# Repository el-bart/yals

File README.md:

# YALS: Yet Another Linear Servo

project to build a linear servo for RC models.

## key project assumptions

* long move range
* digital position control
* digital feedback on current servo position
* 12V power supply (directly from battery)
* does not consume power when not moving, while still keeping position
* possible magnetic coupling with element moved
* programmable and persistent:
  * min / max positions
  * LED brightness

## building

TL;DR just run `make` from project's root directory.

toolchain has been dockerized.
to make usage more convenient, there's a top-level `Makefile` to run all the elements.
it automatically keeps dependsncies in place.

generated stuff:
* 3D models for printing:
  * all in: `body/build/voron_24_revo/petg/strength/*.gcode`
  * note that there can be >1 carriage to choose from
* electronics (HW):
  * gerber files for PCB: `board/hw/build/gerber.zip`
  * PCB assembly: `board/hw/build/graphics/`
  * BOM: `board/hw/build/bom.csv`
* software (SW):
  * to flash use `./rp2020_sdk rp2040_flash <name_of_binary.elf>` from `board/sw` directory
  * binaries:
    * controller to flash (production): `board/sw/build/rp2040/servo_ctrl.elf`
    * manual tests (for validation of HW assembly):
      * `board/sw/build/rp2040/Hal/rp2040/Hal_*.mtest.elf`
      * `board/sw/build/rp2040/Utils/*.mtest.elf`

## assembly

### BOM
* 1x PCB assembly (see `baord/hw` - build it to get `board/hw/build/bom.csv`)
* 1x MT44 DC motor
* 2x 3x7x3mm ball bearing
* 1x 3mm-3mm universal joing (aka: Cardan joint)
* 1x 3mm threaded rod (~12cm)
* 3x 3mm threaded inset (1x for carriage and 2x for engine)
* 2x M3x14 screws (engine mount)
* 2x M3x10 screws (potentiometer mount)

### tools
* soldering iron
* 3D printer for YALS' body
* hex-key set
* pico-probe or raspberry pi SBC to flash `rp2040` µC

## FAQ

### why no position-watchdog?
µC has internal watchdog, that kicks in in case software gets stuck.

however there's no application-level watchdog (e.g. a dedicated command that'd require a new command reception in a given time)
as servo does not go bonkers when signal is lost (as typical, cheap, analog do).
instead it keeps current position effortlessly.
on start, current position is retained as well.
therefor there's no need to perform any special actions, when no new command is received.

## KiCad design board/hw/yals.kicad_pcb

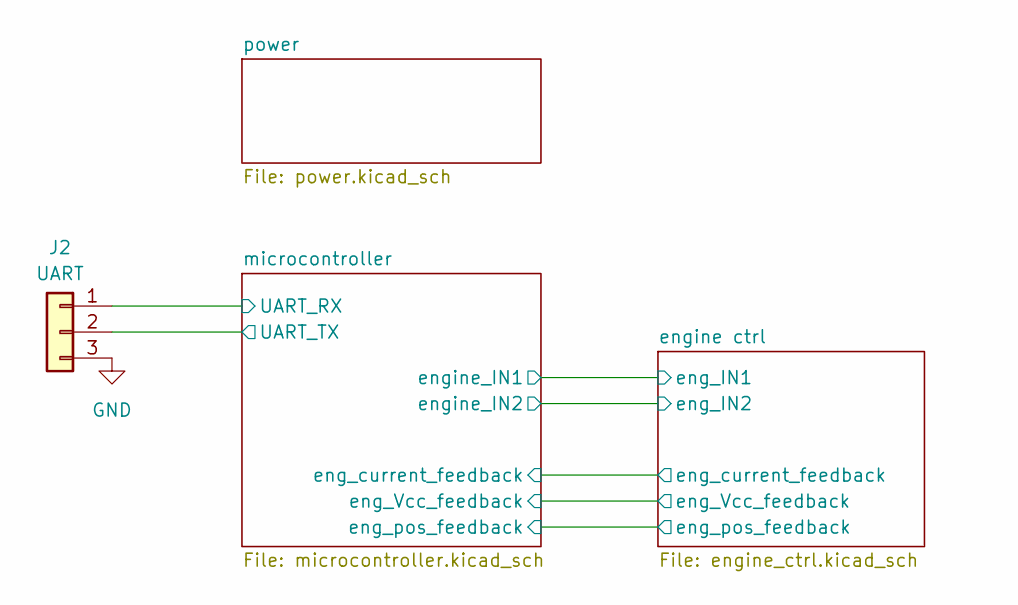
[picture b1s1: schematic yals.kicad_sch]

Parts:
J2: UART; PinHeader_1x03_P2.54mm_Vertical

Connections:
/microcontroller/UART_RX: J2.1; also elsewhere on the board
/microcontroller/UART_TX: J2.2; also elsewhere on the board
GND: J2.3; also elsewhere on the board

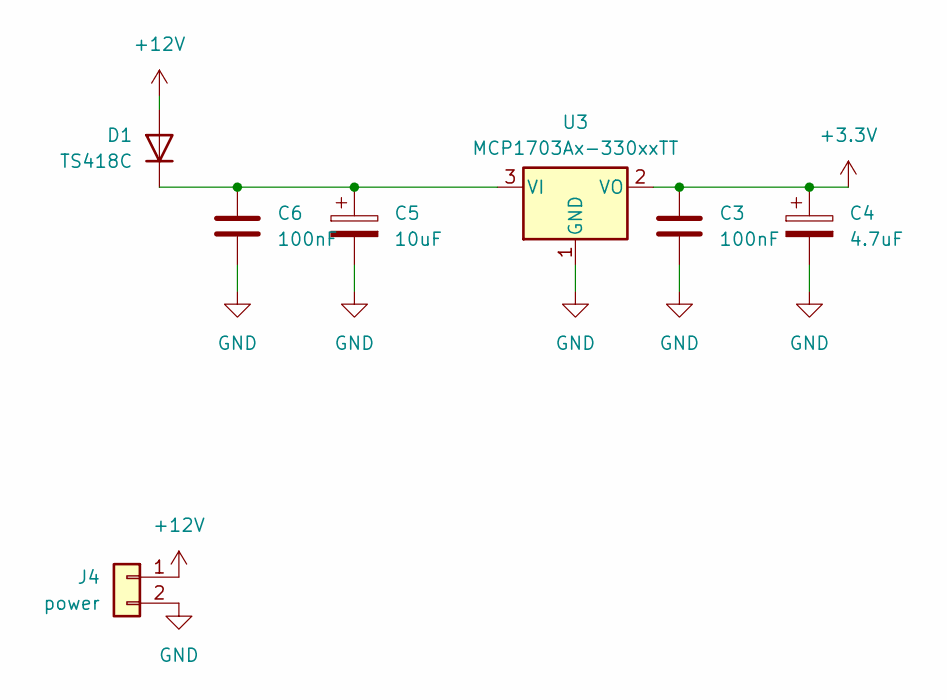
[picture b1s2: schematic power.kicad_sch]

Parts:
C3, C6: 100nF; C_1206_3216Metric
C4: 4.7uF; CP_Elec_5x4.5
C5: 10uF; CP_Elec_5x4.5
D1: TS418C; D_0603_1608Metric
J4: power; PinHeader_1x02_P2.54mm_Vertical
U3: MCP1703Ax-330xxTT; SOT-23

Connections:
+3.3V: C3.1, C4.1, U3.2 (VO); also elsewhere on the board
+12V: D1.2 (A), J4.1; also elsewhere on the board
GND: C3.2, C4.2, C5.2, C6.2, J4.2, U3.1 (GND); also elsewhere on the board
unnamed: C5.1, C6.1, D1.1 (K), U3.3 (VI)

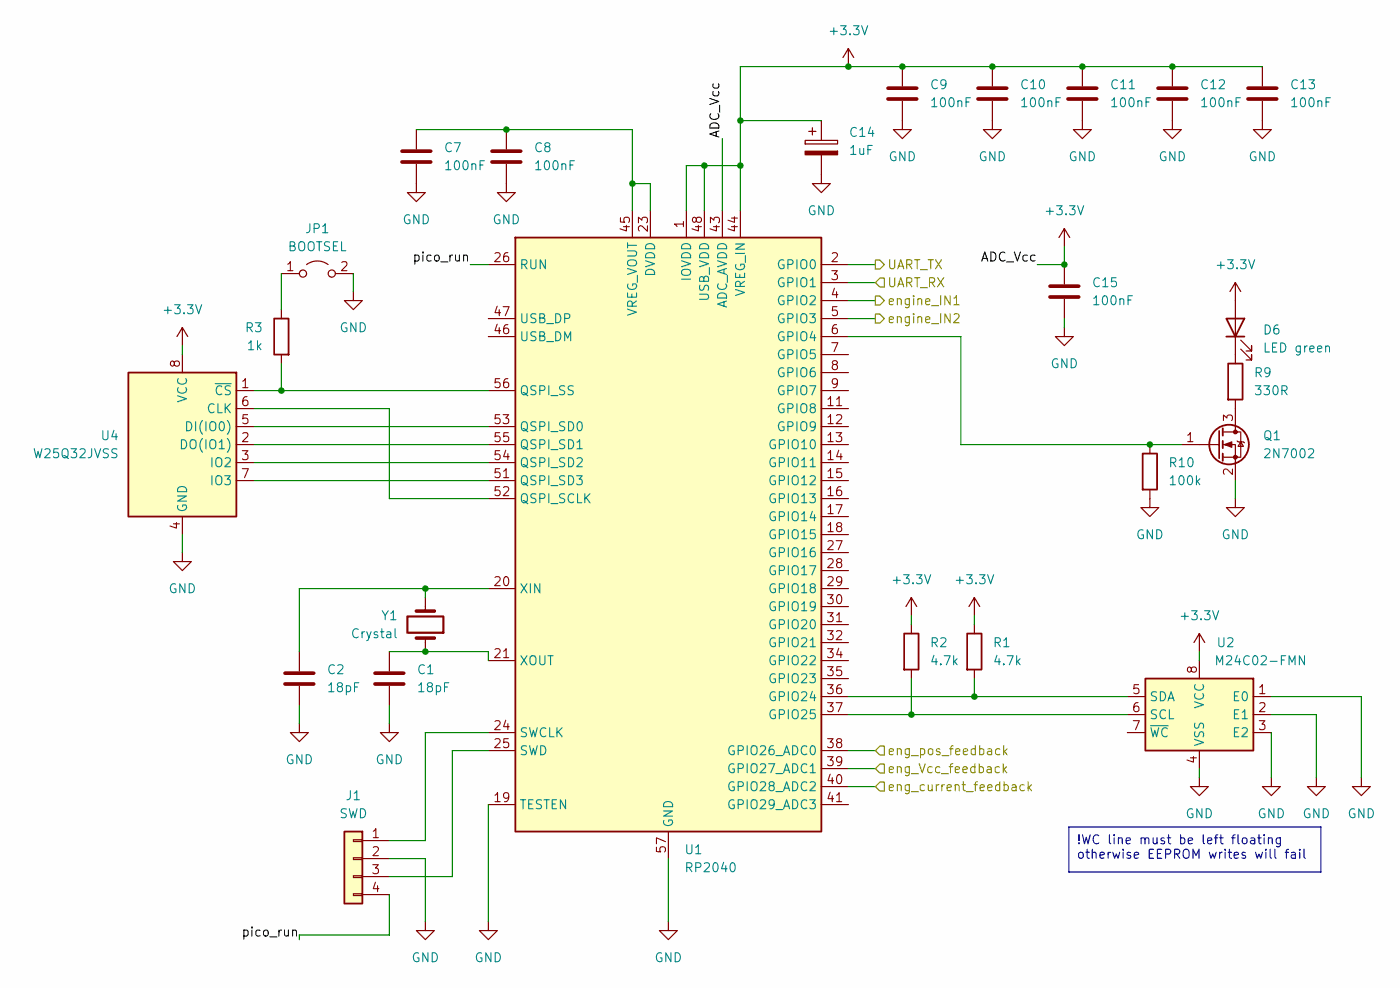
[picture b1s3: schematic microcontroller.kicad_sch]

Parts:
C1, C2: 18pF; C_0603_1608Metric
C7, C8, C9, C10, C11, C12, C13, C15: 100nF; C_1206_3216Metric
C14: 1uF; CP_Elec_5x4.5
D6: LED green; LED_0805_2012Metric_Pad1.15x1.40mm_HandSolder
J1: SWD; PinHeader_1x04_P2.54mm_Vertical
JP1: BOOTSEL; PinHeader_1x02_P2.54mm_Vertical
Q1: 2N7002; SOT-23
R1, R2: 4.7k; R_0603_1608Metric
R3: 1k; R_0603_1608Metric
R9: 330R; R_0805_2012Metric
R10: 100k; R_0603_1608Metric
U1: RP2040; QFN-56-1EP_7x7mm_P0.4mm_EP3.2x3.2mm
U2: M24C02-FMN; SOIC-8_3.9x4.9mm_P1.27mm
U4: W25Q32JVSS; SOIC-8_5.23x5.23mm_P1.27mm
Y1: Crystal; Crystal_SMD_SeikoEpson_MA505-2Pin_12.7x5.1mm

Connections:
+3.3V: C9.1, C10.1, C11.1, C12.1, C13.1, C14.1, C15.1, D6.2 (A), R1.1, R2.1, U1.1 (IOVDD), U1.10 (IOVDD), U1.22 (IOVDD), U1.33 (IOVDD), U1.42 (IOVDD), U1.43 (ADC_AVDD), U1.44 (VREG_IN), U1.48 (USB_VDD), U1.49 (IOVDD), U2.8 (VCC), U4.8 (VCC); also elsewhere on the board
/engine ctrl/eng_IN1: U1.4 (GPIO2); also elsewhere on the board
/engine ctrl/eng_IN2: U1.5 (GPIO3); also elsewhere on the board
/engine ctrl/eng_Vcc_feedback: U1.39 (GPIO27_ADC1); also elsewhere on the board
/engine ctrl/eng_current_feedback: U1.40 (GPIO28_ADC2); also elsewhere on the board
/engine ctrl/eng_pos_feedback: U1.38 (GPIO26_ADC0); also elsewhere on the board
/microcontroller/UART_RX: U1.3 (GPIO1); also elsewhere on the board
/microcontroller/UART_TX: U1.2 (GPIO0); also elsewhere on the board
/microcontroller/pico_run: J1.4, U1.26 (RUN)
GND: C1.2, C2.2, C7.2, C8.2, C9.2, C10.2, C11.2, C12.2, C13.2, C14.2, C15.2, J1.2, JP1.2 (B), Q1.2 (S), R10.2, U1.19 (TESTEN), U1.57 (GND), U2.1 (E0), U2.2 (E1), U2.3 (E2), U2.4 (VSS), U4.4 (GND); also elsewhere on the board
unnamed: D6.1 (K), R9.1
unnamed: J1.1, U1.24 (SWCLK)
unnamed: J1.3, U1.25 (SWD)
unnamed: JP1.1 (A), R3.1
unnamed: Q1.3 (D), R9.2
unnamed: Q1.1 (G), R10.1, U1.6 (GPIO4)
unnamed: R1.2, U1.36 (GPIO24), U2.5 (SDA)
unnamed: R2.2, U1.37 (GPIO25), U2.6 (SCL)
unnamed: U1.52 (QSPI_SCLK), U4.6 (CLK)
unnamed: U1.53 (QSPI_SD0), U4.5 (DI(IO0))
unnamed: U1.55 (QSPI_SD1), U4.2 (DO(IO1))
unnamed: U1.54 (QSPI_SD2), U4.3 (IO2)
unnamed: U1.51 (QSPI_SD3), U4.7 (IO3)
unnamed: R3.2, U1.56 (QSPI_SS), U4.1 (~CS)
unnamed: C7.1, C8.1, U1.23 (DVDD), U1.45 (VREG_VOUT), U1.50 (DVDD)
unnamed: C2.1, U1.20 (XIN), Y1.2
unnamed: C1.1, U1.21 (XOUT), Y1.1

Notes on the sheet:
!WC line must be left floating otherwise EEPROM writes will fail

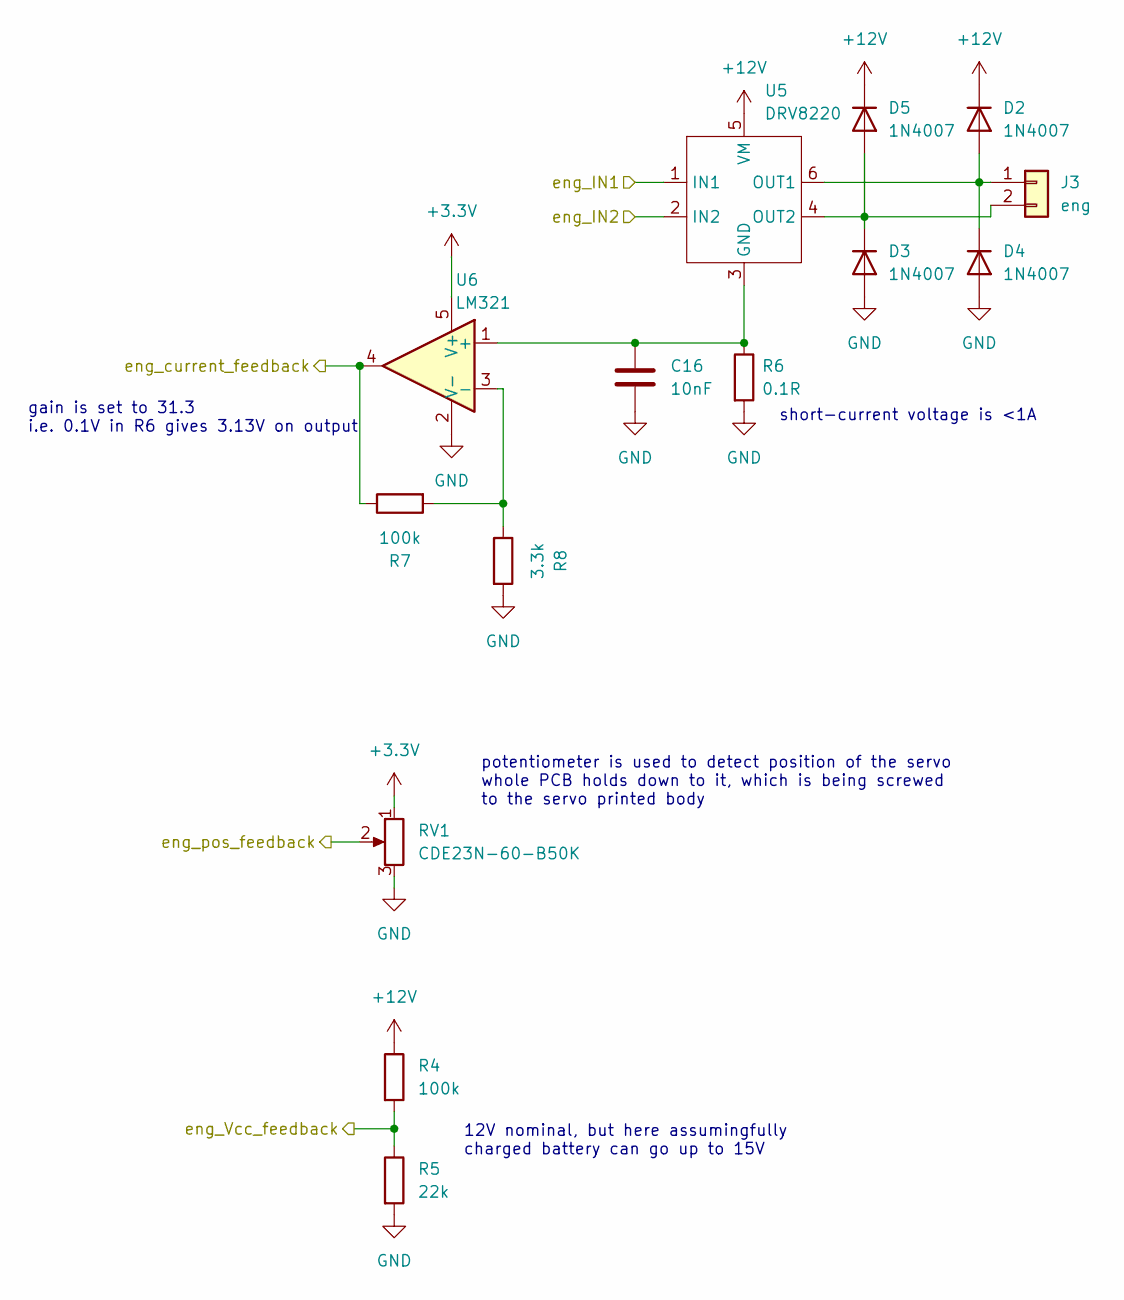
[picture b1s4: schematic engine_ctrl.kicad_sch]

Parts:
C16: 10nF; C_1206_3216Metric
D2, D3, D4, D5: 1N4007; D_SOD-123F
J3: eng; PinHeader_1x02_P2.54mm_Vertical
R4, R7: 100k; R_0603_1608Metric
R5: 22k; R_0603_1608Metric
R6: 0.1R; R_1206_3216Metric
R8: 3.3k; R_0603_1608Metric
RV1: CDE23N-60-B50K
U5: DRV8220; SOT-563
U6: LM321; SOT-23-5

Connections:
+3.3V: RV1.1, U6.5 (V+); also elsewhere on the board
+12V: D2.1 (K), D5.1 (K), R4.1, U5.5 (VM); also elsewhere on the board
/engine ctrl/eng_IN1: U5.1 (IN1); also elsewhere on the board
/engine ctrl/eng_IN2: U5.2 (IN2); also elsewhere on the board
/engine ctrl/eng_Vcc_feedback: R4.2, R5.1; also elsewhere on the board
/engine ctrl/eng_current_feedback: R7.1, U6.4; also elsewhere on the board
/engine ctrl/eng_pos_feedback: RV1.2; also elsewhere on the board
GND: C16.2, D3.2 (A), D4.2 (A), R5.2, R6.2, R8.2, RV1.3, U6.2 (V-); also elsewhere on the board
unnamed: D2.2 (A), D4.1 (K), J3.1, U5.6 (OUT1)
unnamed: D3.1 (K), D5.2 (A), J3.2, U5.4 (OUT2)
unnamed: C16.1, R6.1, U5.3 (GND), U6.1 (+)
unnamed: R7.2, R8.1, U6.3 (-)

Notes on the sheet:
short-current voltage is <1A
12V nominal, but here assumingfully charged battery can go up to 15V
potentiometer is used to detect position of the servo whole PCB holds down to it, which is being screwed to the servo printed body
gain is set to 31.3 i.e. 0.1V in R6 gives 3.13V on output

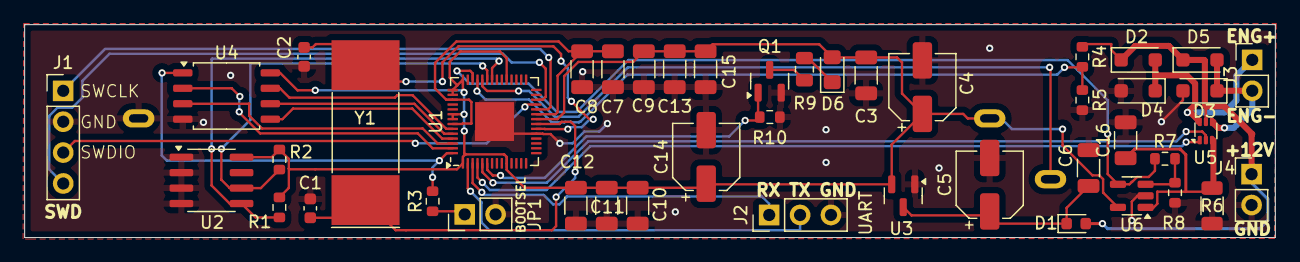
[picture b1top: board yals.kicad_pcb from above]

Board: 2 copper layers, 102.9 x 17.5 mm, 46 parts (1 on the bottom side), 33 nets.

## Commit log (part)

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2024-03-30 rp2040 and its connections are nearly done (still missing power-measuring capabilities)
2024-03-30 TODOs on engine part and voltage measurements
2024-03-31 symbol for DRV8220 dual H-bridge
2024-03-31 added engine driver with votage measuring resistor to schematics
2024-03-31 fixed pin directions for engine ctrl and UART
2024-04-07 voltage measuing capacity has been added
2024-04-07 added current measuing circuit
2024-04-07 engine ctrl and feedback loop elements placed
2024-04-07 fixed OpAmp description wrt gain
2024-04-07 initial placement of all components
2024-04-07 monior repositioning to avoid PCB edges and better alignment of parallel elements
2024-04-07 added green LED, controllable from µC
2024-04-07 added top+bottom GND plane
2024-04-07 added vias to have GND coverage on both layers
2024-04-07 increased height of the board by 1mm, to accomodate more wireing that's needed there
2024-04-07 fixed all the DRC errors and warning on the PCB
2024-04-07 added proper soldermask marking of all I/O pins + moved element designators to rightful places
2024-04-07 PCB mock added
2024-04-07 added PCB to main servo body visualization as a mock
2024-04-18 RP2040 SDK
2024-04-18 blinking app example - WIP
2024-04-19 added some TODOs for board
2024-04-19 TODO: consider hand-soldering pads
2024-04-23 20k -> 22k
2024-04-23 kicad DRC exclusion
2024-06-10 added working CMakeLists.txt for the board
2024-06-10 removed unused C example
2024-06-10 updated helper script for flashing target
2024-06-24 fixed indentation
2024-06-24 experimenting with custom board header file
2024-06-24 common var for delay (50% duty cycle)
2024-06-24 moved clock settings to a separate file
2024-06-24 added reading character from uart and removed LED ctrl
2024-07-13 position adjusted for consistency
2024-11-14 model -> body (to make it more meaningful)
2024-11-14 RP2040 SDK update
2024-11-14 build for Voron 2.4 instead of anycubic
2024-11-14 pcb.stl must be ignored - link won't work with docker image
2024-11-15 pico SDK w/o depth limitation
2024-11-15 added mtest for engine
2024-11-15 ADC for engine's Vcc feedback mtest added
2024-11-15 ADC for engine current feedback added
2024-11-15 marked basic tests as done
2024-11-18 rewriten engine's mtest to use new HAL
2024-11-18 direct LED control
2024-11-18 helper scritp for building, uploading and testing 1 binary
2024-11-18 added option to compile things only
2024-11-18 UART serial example
2024-11-18 added mtest for position feedback
2024-11-18 added missing header
2024-11-18 ADC test for engine current reworked to use common HAL code
2024-11-18 include cleanup
2024-11-18 simplify meothd naming
2024-11-18 added common code for building binaries
2024-11-18 added per-HAL split in SDK
2024-11-18 HAL for local simulation
2024-11-18 enabled simulation (native) build again
2024-11-18 test pass
2024-11-18 listing all *.elf bins after rp2040 build
2024-11-18 1st smoke test for simulator access
2024-11-18 Hal::All is a structure
2024-11-18 show failed tests on error
2024-11-18 HAL layer now has a common part, that's HW-independent, to make interfaces nicer
2024-11-18 fixed order of includes
2024-11-18 added missing headers for HAL of rp2040
2024-11-18 protocol definition
2024-11-19 try -> compile_and_flash
2024-11-19 removed old flashing helper script
2024-11-19 described first byte of in more details + moved split to 6-bit frame ID
2024-11-19 reorganized header byte, to make more wiggle room of rfuture (if needed)
2024-11-19 Io::Frame + tests: placehoders
2024-11-19 Buffer class implemented and tested
2024-11-19 Mtu moved to separate file (WIP)
2024-11-19 MTU extraction is now completed
2024-11-19 added description of the Frame
2024-11-19 hex-to-byte conversion
2024-11-19 to_hex conversion
2024-11-19 greately simplified I/O protocol + mad it human readable
2024-11-19 removed Frame
2024-11-19 Mtu -> Line
2024-11-19 sizes are now of size_t type
2024-11-19 fixed som minor sytax things
2024-11-19 fixed extraction of max line in 1 go
2024-11-19 max line size now includes space for EOL in the internal FIFO on µC
2024-11-19 msg can only be 30B, to make sure it fits into the buffer
2024-11-19 documented that each reponse always contains a checksum
2024-11-19 placeholder for processor of messages
2024-11-19 checksum checking code
2024-11-19 WIp for process() UTs
2024-11-19 added -Wall -Werror to compilation
2024-11-19 1-char command from now on
2024-11-19 decoding request returns optional values, as it may fail
2024-11-19 persisten config is now correctly parsed
2024-11-19 added unique cmd char to getting servo position, too
2024-11-19 getting telemetry implemented and tested
2024-11-19 setting LED brightness is now completed
2024-11-19 common -> read_number()
2024-11-19 setting max servo position
2024-11-19 setting servo position is now programmed
2024-11-19 added missing headers
2024-11-19 fixed compilation errors
2024-11-19 fixed ODR for Hal::sim()
2024-11-19 added placeholder for UTs for Controller
2024-11-19 added min/max positions for simulation
2024-11-20 aligned all floats to be in 0..1 instead of percent (for consistency)
2024-11-20 fixed marker support in EEPROM
2024-11-20 removed solved TODOs
2024-11-20 added list of features
2024-11-20 TODO added
2024-11-20 EEPROM mtest is ready
2024-11-20 EEPROM handling - WIP
2024-11-20 renmaed bus scanner for I2C
2024-11-20 fixed incorrect default value
2024-11-20 Hal::EEPROM API now can report R/W errors
2024-11-20 nicer outptu formatting
2024-11-20 trimming input value - just in case
2024-11-20 raw EEPROM I/O mtest
2024-11-20 printing size of *.bin, not *.elf
2024-11-20 some throttling + pruging + force reading the 1st time
2024-11-20 TODO to fix broken EEPROM
2024-11-20 latest status on EEPROM I/O - still not working...
2024-11-20 added TX/RX buffers to context
2024-11-20 Sim's UART I/O is now deque based
2024-11-20 removed terminatiing zero override
2024-11-20 TODO for LED persistency added
2024-11-20 added LED_brightness to setpoints
2024-11-20 buffer can now hold up to 8 full lines
2024-11-20 added handing of telemetry
2024-11-20 EEPROM now can store LED brightness info as well
2024-11-20 added LED brightness handing to protocol
2024-11-20 comments updated
2024-11-20 fixed handling of brightness in test stack
2024-11-20 removed redundant place for setpoints defaults
2024-11-20 fixed EEPROM settings writing for hight values
2024-11-20 added error handling on writing LED brightness to EEPROM
2024-11-20 fixed variable used
2024-11-20 added setting max servo position
2024-11-20 PoC for max comparins tests
2024-11-20 EEPROM sim is now properly handing numerics
2024-11-20 added handlign of settin out-of-range positions
2024-11-20 preped up tests for Set_min_servo_position
2024-11-20 added handing of movement on setting min and erro if max < min
2024-11-20 settin max position now also updates setpoint for servo
2024-11-20 common converter from float to u32 in Handler
2024-11-20 fixed test for getting presets
2024-11-20 removed unnedded TODO from main loop
2024-11-20 enlarged max line lenght
2024-11-20 fixed Ping's response + UT
2024-11-20 added proper handling of bigger reply strings from Ping
2024-11-20 fixed compilation
2024-11-20 changed version.cpp generation scheme
2024-11-20 indentation and style unification
2024-11-20 moved git.cmake to a separate dir
2024-11-20 added more comments and nicer formatting
2024-11-21 added a couple default settings
2024-11-21 added clock to Hal::All + Sim
2024-11-21 writer helpers are now common for UART and EEPROM UTs, too
2024-11-21 added Ticks and some absic operators around these
2024-11-21 added purge_rx() helper
2024-11-21 engine mtest now allows for an explicit control
2024-11-21 adjusted time constants to make it easier to steer manually
2024-11-21 fixed direction of position feedback to match circut
2024-11-21 added units for tolerance value
2024-11-21 added some more comments
2024-11-21 placeholder for engine controller and its UTs
2024-11-21 initial structure for algo
2024-11-21 updated Engine and sim.ut.cpp to apply correct directions of travel (i.e. consistent with real HW)
2024-11-21 adjusted when full throttle shall be applied
2024-11-21 draft of engine control algo
2024-11-21 min/max are now calculated based on potentiometer precision (percentage)
2024-11-21 default LED brightness is now moved to config as well
2024-11-21 comments and units
2024-11-21 integrated Engine_controller to Controller
2024-11-21 increased sampling frequency in position mtest
2024-11-21 * added predefined control loop frequency to aim for * adjusted config params to minimize a risk of moving back-and-forth
2024-11-21 main control loop is now obeying frequency for engine control - I/O runs at full throttle
2024-11-21 added tests for Controller::update_only()
2024-11-21 placeholder for Handler test
2024-11-21 added convenience limits for absolute min/max values
2024-11-21 abs min/max are now the defaults in SW
2024-11-21 fixed UT for max abs value when setting position
2024-11-21 added handling of abs max value when setting max position
2024-11-21 added tests for error handling in Controller
2024-11-21 Approx(): epsilon() -> margin()
2024-11-21 algo for progressing with engine movement is now a separate code
2024-11-21 test for histeresis
2024-11-21 no_movement helper
2024-11-21 more features listed
2024-11-21 moved actual udpate action to a helper method
2024-11-21 settings updated to high prevision w/o constant adjustments
2024-11-21 added simulation of stall + recovery
2024-11-21 move to use a common constant for travel time
2024-11-22 added servo speed and travel time
2024-11-22 draft of engine jogging test app
2024-11-22 sleep() Hal helper
2024-11-22 adjsuted histeresis
2024-11-22 fixed test to keep the position while idling
2024-11-22 control_loop_time -> control_loop_time_s
2024-11-22 engine mtest now does left/right presets separately, on explicit key press
2024-11-22 removed more debug prints
2024-11-22 removed debug header
2024-11-22 added lower bound to ensure dt_s is never 0 (even right after start)
2024-11-22 another mtest that drioves engine back and forth across different positions
2024-11-22 rapid jog mtest added
2024-11-22 SW is ~complete - removing from TODOs
2024-11-22 Engine_controller also checks absolute HW limits
2024-11-22 added Watchdog to Hal (not used anywhere yet)
2024-11-22 added comment on reboot frequency with watchdog
2024-11-22 added watchdog reset to Controller's main loop
2024-11-22 added Hal::Watchdog API to check if watchod was the reason for a reboot
2024-11-22 added UT for displaying warning when reboot via watchdog was detected
2024-11-22 added TODO for LED blinking
2024-11-22 added release notes file
2024-11-22 RP2040 SDK bump (latest scripts)
2024-11-24 added basic stuff needed for assembly
2024-11-26 removed unneeded includes dir
2024-12-04 added holes into release notes
2024-12-05 helper makefile to run builds and flashing
2024-12-05 fixed closing quote
2024-12-05 draft of a unified build
2024-12-05 fixed path to pcb.stl
2024-12-05 building instructions added
2024-12-10 put down the solution for EEPROM issue
2024-12-10 cleanup of EEPROM code, after latest tests - ~WC was the problem after all...
2024-12-10 ~WC pin of EEPROM chip is left floating, to make writes possible
2024-12-10 removed unneeded I2C/EEPROM debugging code, that's no longer relevant
2024-12-10 added note that EEPROM is now working as expected
2024-12-11 added static_assert for safe watchdog value, to ensure some sanity checks are in place
2024-12-12 added sanitization of min_position when read from EEPROM
2024-12-12 min / max is now going to default value if out of range
2024-12-12 added LED brightness sanitization test (not testable yet - commented out)
2024-12-12 adjusted EEPROM impl for rp2040 to new API
2024-12-12 * added and tested LED-brightness sanitization * added test to ensure all EEPROM values remain as-is, in case there are no issues
2024-12-12 added not on EEPROM sanitization
2024-12-12 v0.4 mark in release notes
2024-12-12 noted persisten config feature
2025-01-29 3D SDK bump
2025-02-23 FAQ: no position-watchdog
